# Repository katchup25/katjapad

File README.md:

# katjapad

A 9-key macropad with a rotary encoder, OLED display, and per-key RGB lighting.
Built for productivity and media control.

## Features
- 9 MX-style switches in a 3x3 grid
- 1 rotary encoder for volume control
- 0.91" OLED display
- Per-key SK6812 MINI-E RGB LEDs
- QMK firmware with custom macros

## Screenshots

### Schematic

### PCB

### Case

## Bill of Materials (BOM)
| Part | Quantity |
|------|----------|
| Seeed XIAO RP2040 | 1 |
| MX-style switches | 9 |
| EC11 Rotary Encoder | 1 |
| 0.91" OLED Display | 1 |
| SK6812 MINI-E LEDs | 9 |
| 1N4148 Diodes | 9 |
| DSA Keycaps | 9 |
| M3x16mm Screws | 6 |
| M3 Heatset Inserts | 6 |

## Firmware
Built with QMK. Key features:
- Top row: Pomodoro timer, to-do list, study playlist (URL macros)
- Middle row: Copy, Paste, New Tab
- Bottom row: Previous, Play/Pause, Next
- Encoder: Volume up/down

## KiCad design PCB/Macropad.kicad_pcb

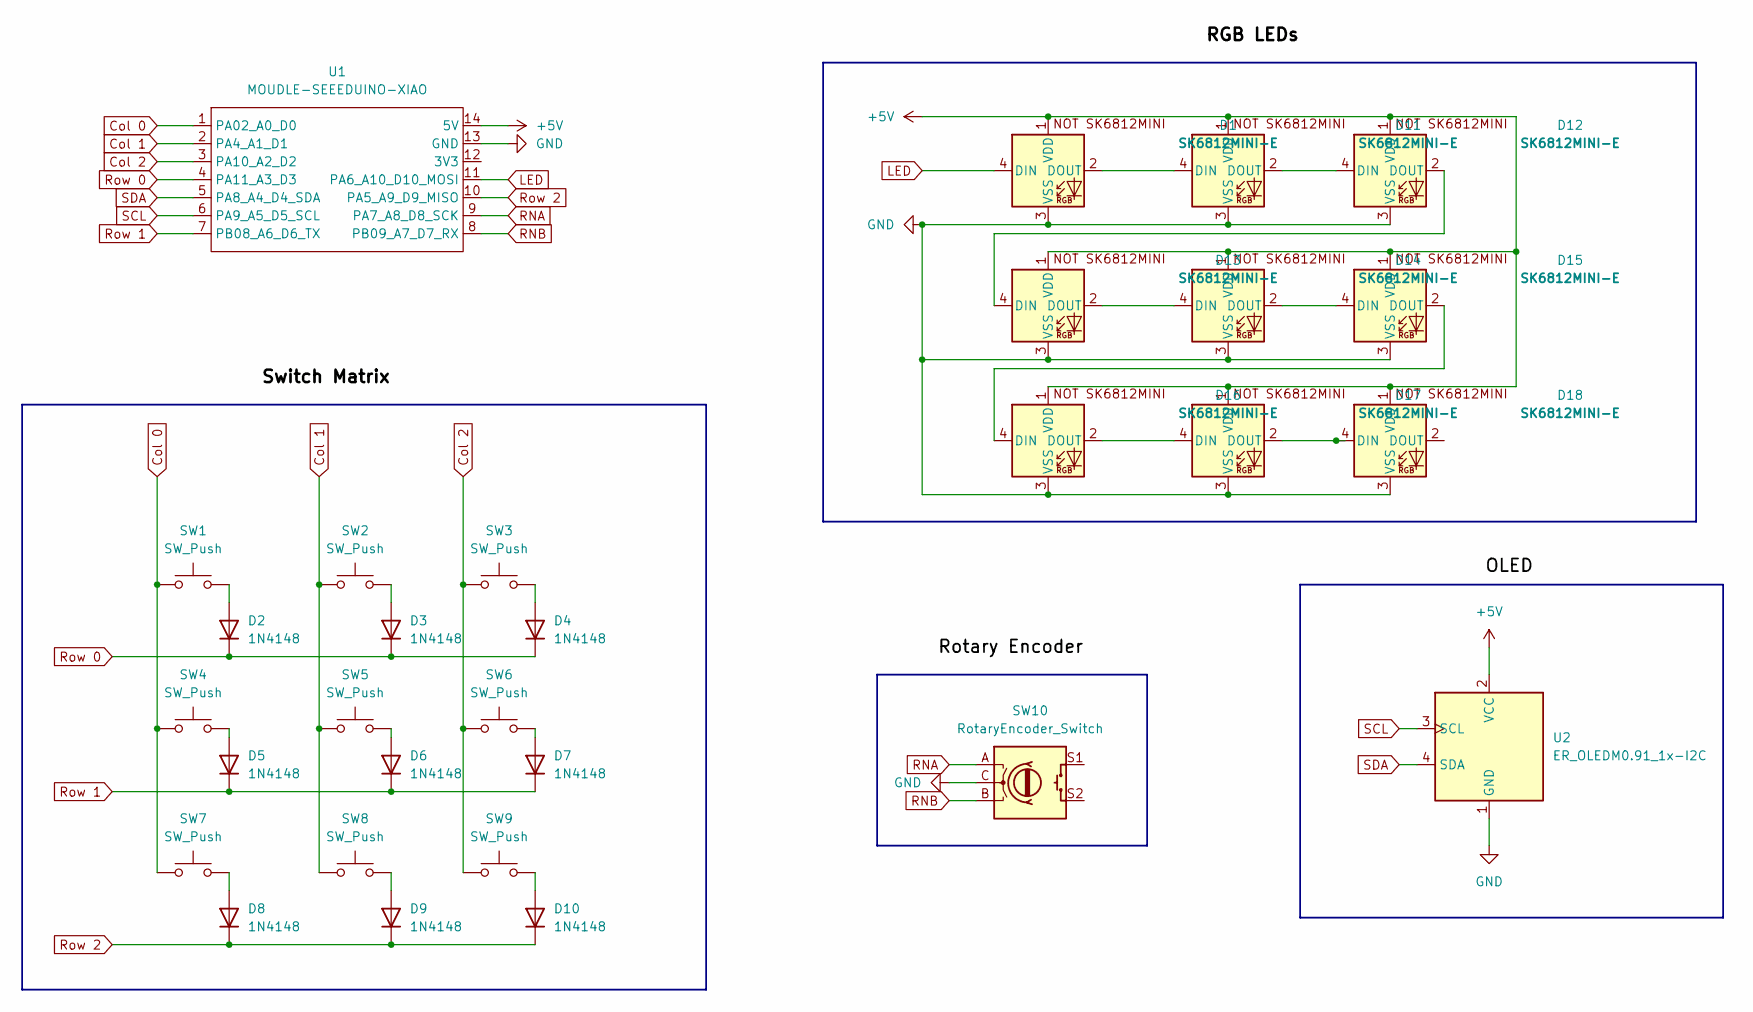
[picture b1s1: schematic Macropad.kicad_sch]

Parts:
D1, D11, D12, D13, D14, D15, D16, D17, D18: SK6812MINI-E; LED_SK6812MINI-E_3.2x2.8mm_P1.5mm_ReverseMount
D2, D3, D4, D5, D6, D7, D8, D9, D10: 1N4148; D_DO-35_SOD27_P7.62mm_Horizontal
SW1, SW2, SW3, SW4, SW5, SW6, SW7, SW8, SW9: SW_Push; SW_Cherry_MX_1.00u_PCB
SW10: RotaryEncoder_Switch; RotaryEncoder_Alps_EC11E-Switch_Vertical_H20mm
U1: MOUDLE-SEEEDUINO-XIAO; XIAO-Generic-Hybrid-14P-2.54-21X17.8MM
U2: ER_OLEDM0.91_1x-I2C

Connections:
+5V: D1.1 (VDD), D11.1 (VDD), D12.1 (VDD), D13.1 (VDD), D14.1 (VDD), D15.1 (VDD), D16.1 (VDD), D17.1 (VDD), D18.1 (VDD), U1.14 (5V), U2.2 (VCC)
Col 0: SW1.1, SW4.1, SW7.1, U1.1 (PA02_A0_D0)
Col 1: SW2.1, SW5.1, SW8.1, U1.2 (PA4_A1_D1)
Col 2: SW3.1, SW6.1, SW9.1, U1.3 (PA10_A2_D2)
GND: D1.3 (VSS), D11.3 (VSS), D12.3 (VSS), D13.3 (VSS), D14.3 (VSS), D15.3 (VSS), D16.3 (VSS), D17.3 (VSS), D18.3 (VSS), SW10.C, U1.13 (GND), U2.1 (GND)
LED: D1.4 (DIN), U1.11 (PA6_A10_D10_MOSI)
unnamed: D1.2 (DOUT), D11.4 (DIN)
unnamed: D2.2 (A), SW1.2
unnamed: D3.2 (A), SW2.2
unnamed: D4.2 (A), SW3.2
unnamed: D5.2 (A), SW4.2
unnamed: D6.2 (A), SW5.2
unnamed: D7.2 (A), SW6.2
unnamed: D8.2 (A), SW7.2
unnamed: D9.2 (A), SW8.2
unnamed: D10.2 (A), SW9.2
unnamed: D11.2 (DOUT), D12.4 (DIN)
unnamed: D12.2 (DOUT), D13.4 (DIN)
unnamed: D13.2 (DOUT), D14.4 (DIN)
unnamed: D14.2 (DOUT), D15.4 (DIN)
unnamed: D15.2 (DOUT), D16.4 (DIN)
unnamed: D16.2 (DOUT), D17.4 (DIN)
unnamed: D17.2 (DOUT), D18.4 (DIN)
RNA: SW10.A, U1.9 (PA7_A8_D8_SCK)
RNB: SW10.B, U1.8 (PB09_A7_D7_RX)
Row 0: D2.1 (K), D3.1 (K), D4.1 (K), U1.4 (PA11_A3_D3)
Row 1: D5.1 (K), D6.1 (K), D7.1 (K), U1.7 (PB08_A6_D6_TX)
Row 2: D8.1 (K), D9.1 (K), D10.1 (K), U1.10 (PA5_A9_D9_MISO)
SCL: U1.6 (PA9_A5_D5_SCL), U2.3 (SCL)
SDA: U1.5 (PA8_A4_D4_SDA), U2.4 (SDA)

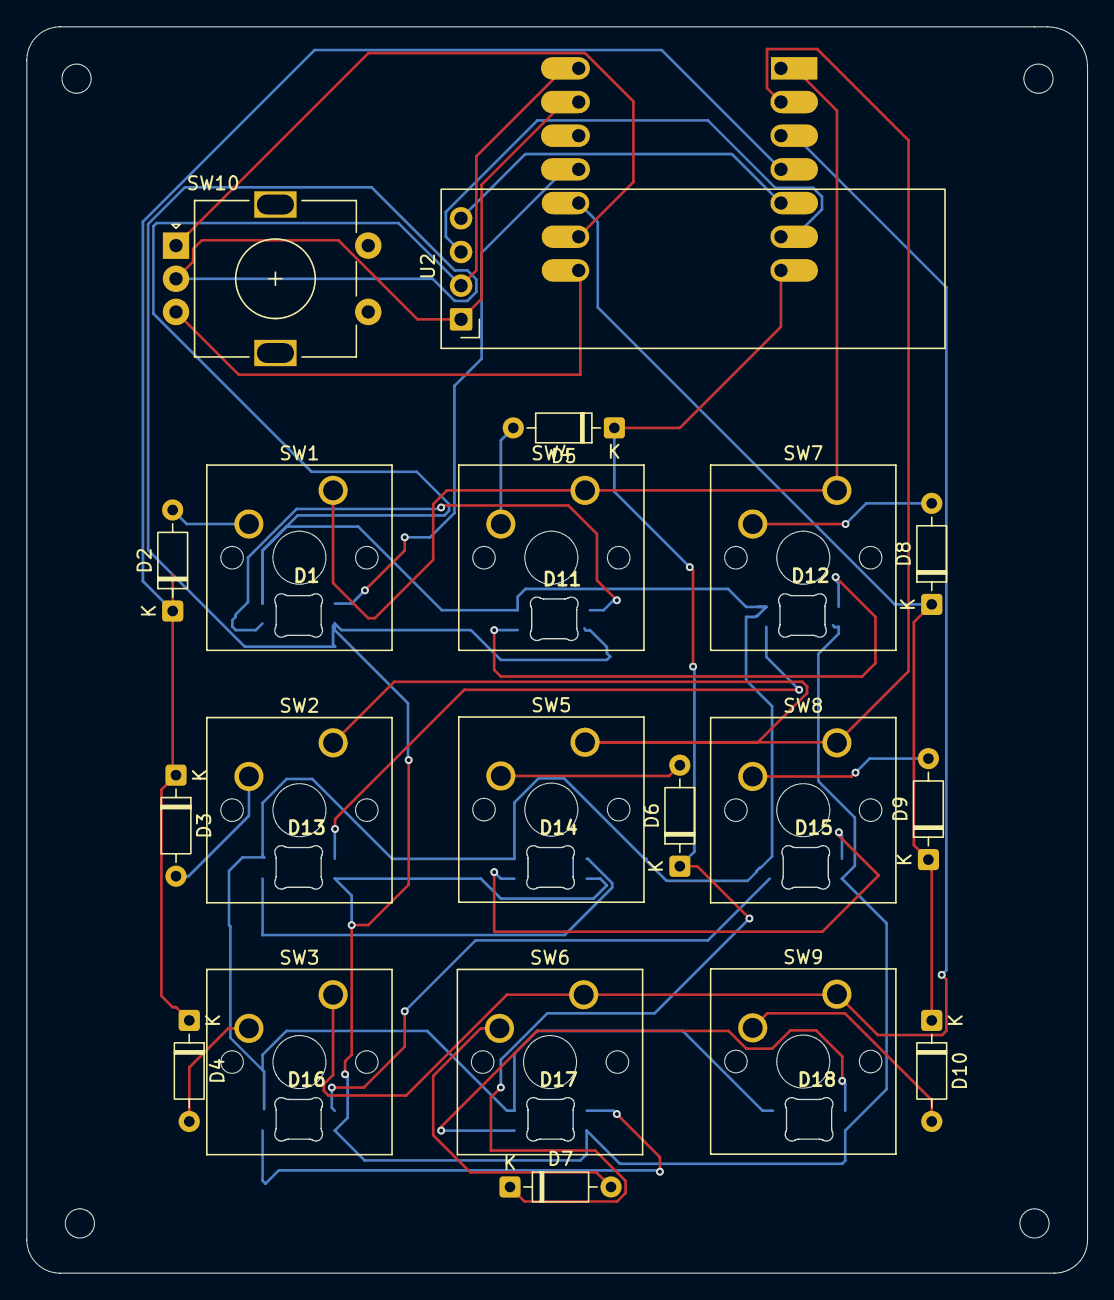
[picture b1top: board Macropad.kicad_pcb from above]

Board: 2 copper layers, 80.0 x 94.0 mm, 30 parts (1 on the bottom side), 30 nets.
